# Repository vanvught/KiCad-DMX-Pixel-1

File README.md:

# KiCad DMX/RDM and Pixel 1-port 

Firmware 

- [https://github.com/vanvught/GD32F103RC-DMX512-RDM](https://github.com/vanvught/GD32F103RC-DMX512-RDM)
- [https://github.com/vanvught/GD32F107RC-DMX512-RDM](https://github.com/vanvught/GD32F107RC-DMX512-RDM)
- [https://github.com/vanvught/GD32F303RC-DMX512-RDM](https://github.com/vanvught/GD32F303RC-DMX512-RDM)

More information [https://www.gd32-dmx.org/pixel.html](https://www.gd32-dmx.org/pixel.html)

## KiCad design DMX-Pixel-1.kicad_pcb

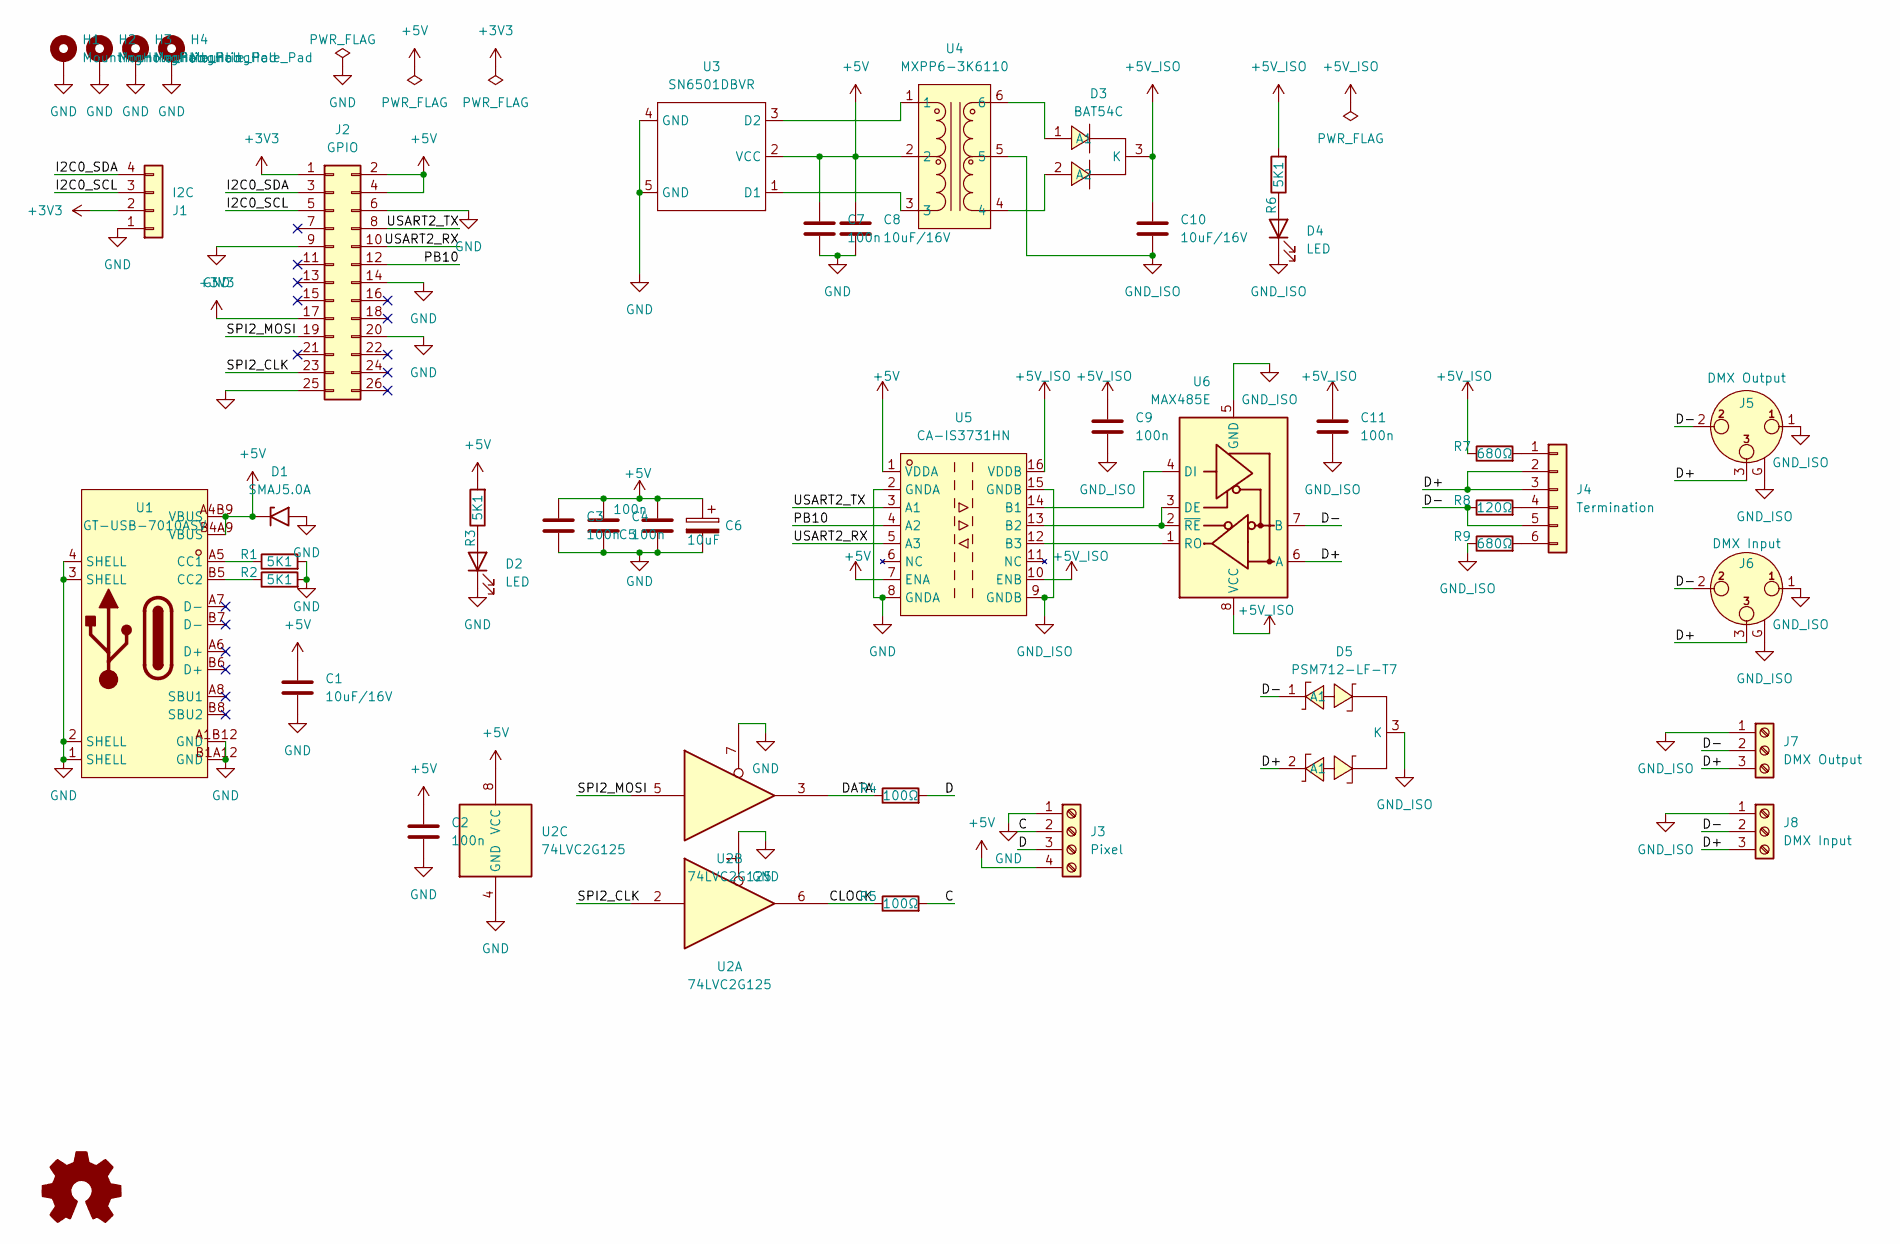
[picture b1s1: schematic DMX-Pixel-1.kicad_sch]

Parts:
C1, C8, C10: 10uF/16V; C_0603_1608Metric; LCSC Part C19702
C2, C3, C4, C5, C7, C9, C11: 100n; C_0603_1608Metric; LCSC Part C14663
C6: 10uF; CP_EIA-3216-18_Kemet-A; LCSC Part C7171
D1: SMAJ5.0A; D_SMA; LCSC Part C113952
D2, D4: LED; LED_0805_2012Metric; LCSC Part C2297
D3: BAT54C; SOT-23-3_L2.9-W1.6-P1.90-LS2.8-BR; MPN BAT54C; LCSC Part C2135
D5: PSM712-LF-T7; SOT-23-3_L3.0-W1.7-P0.95-LS2.9-BR; MPN PSM712-LF-T7; LCSC Part C32677
H1, H2, H3, H4: MountingHole_Pad; MountingHole_2.7mm_M2.5_Pad
J1: I2C; PinHeader_1x04_P2.54mm_Vertical
J2: GPIO; PinSocket_2x13_P2.54mm_Vertical
J3: Pixel; TerminalBlock_MetzConnect_Type094_RT03504HBLU_1x04_P5.00mm_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
J4: Termination; PinHeader_1x06_P2.54mm_Vertical
J5: DMX Output; Jack_XLR_Neutrik_NC3FAH2_Horizontal
J6: DMX Input; Jack_XLR_Neutrik_NC3MAH_Horizontal
J7: DMX Output; TerminalBlock_MetzConnect_Type094_RT03503HBLU_1x03_P5.00mm_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
J8: DMX Input; TerminalBlock_MetzConnect_Type094_RT03503HBLU_1x03_P5.00mm_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
R1, R2, R3, R6: 5K1; R_0603_1608Metric; LCSC Part C23186
R4, R5: 100Ω; R_0603_1608Metric; LCSC Part C22775
R7, R9: 680Ω; R_0603_1608Metric; LCSC Part C23228
R8: 120Ω; R_0603_1608Metric; LCSC Part C22787
SYM1: Logo_Open_Hardware_Small; OSHW-Logo_7.5x8mm_SilkScreen
U1: GT-USB-7010ASV; USB-C-SMD_G-SWITCH_GT-USB-7010ASV; MPN GT-USB-7010ASV; LCSC Part C2988369
U2: 74LVC2G125; SM8_L3.2-W2.9-P0.65-LS4.3-BR; LCSC Part C206035
U3: SN6501DBVR; SOT-23-5_L3.0-W1.7-P0.95-LS2.8-BR; MPN SN6501DBVR; LCSC Part C49451
U4: MXPP6-3K6110; XFMR-SMD_L7.1-W6.6-P2.54_LT31-120; MPN MXPP6-3K6110; LCSC Part C19943838
U5: CA-IS3731HN; SOIC-16_L9.9-W3.9-P1.27-LS6.0-BL; MPN CA-IS3731HN; LCSC Part C428880
U6: MAX485E; SOIC-8_3.9x4.9mm_P1.27mm; LCSC Part C23492

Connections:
+3V3: J1.2, J2.1, J2.17
+5V: C1.1, C2.1, C3.1, C4.1, C5.2, C6.1, C7.1, C8.1, D1.1 (A1), J2.2, J2.4, J3.4, R3.2, U1.A4B9 (VBUS), U1.B4A9 (VBUS), U2.8 (VCC), U3.2 (VCC), U4.2, U5.1 (VDDA), U5.7 (ENA)
+5V_ISO: C9.1, C10.1, C11.1, D3.3 (K), R6.2, R7.1, U5.10 (ENB), U5.16 (VDDB), U6.8 (VCC)
/C: J3.2, R5.2
/CLOCK: R5.1, U2.6
/D: J3.3, R4.2
/D+: D5.2 (A1), J4.2, J4.3, J5.3, J6.3, J7.3, J8.3, U6.6 (A)
/D-: D5.1 (A1), J4.5, J5.2, J6.2, J7.2, J8.2, R8.1, U6.7 (B)
/DATA: R4.1, U2.3
/I2C0_SCL: J1.3, J2.5
/I2C0_SDA: J1.4, J2.3
/PB10: J2.12, U5.4 (A2)
/SPI2_CLK: J2.23, U2.2
/SPI2_MOSI: J2.19, U2.5
/USART2_RX: J2.10, U5.5 (A3)
/USART2_TX: J2.8, U5.3 (A1)
GND: C1.2, C2.2, C3.2, C4.2, C5.1, C6.2, C7.2, C8.2, D1.2 (A2), D2.1 (K), H1.1 (1_1), H2.1 (1_1), H3.1 (1_1), H4.1 (1_1), J1.1, J2.6, J2.9, J2.14, J2.20, J2.25, J3.1, R1.2, R2.2, U1.1 (SHELL), U1.2 (SHELL), U1.3 (SHELL), U1.4 (SHELL), U1.A1B12 (GND), U1.B1A12 (GND), U2.1, U2.4 (GND), U2.7, U3.4 (GND), U3.5 (GND), U5.2 (GNDA), U5.8 (GNDA)
GND_ISO: C9.2, C10.2, C11.2, D4.1 (K), D5.3 (K), J5.1, J5.G, J6.1, J6.G, J7.1, J8.1, R9.1, U4.5, U5.9 (GNDB), U5.15 (GNDB), U6.5 (GND)
unnamed: D2.2 (A), R3.1
unnamed: D3.1 (A1), U4.6
unnamed: D3.2 (A2), U4.4
unnamed: D4.2 (A), R6.1
unnamed: J4.1, R7.2
unnamed: J4.4, R8.2
unnamed: J4.6, R9.2
unnamed: R1.1, U1.A5 (CC1)
unnamed: R2.1, U1.B5 (CC2)
unnamed: U3.1 (D1), U4.3
unnamed: U3.3 (D2), U4.1
unnamed: U5.14 (B1), U6.4 (DI)
unnamed: U5.13 (B2), U6.2 (~RE), U6.3 (DE)
unnamed: U5.12 (B3), U6.1 (RO)

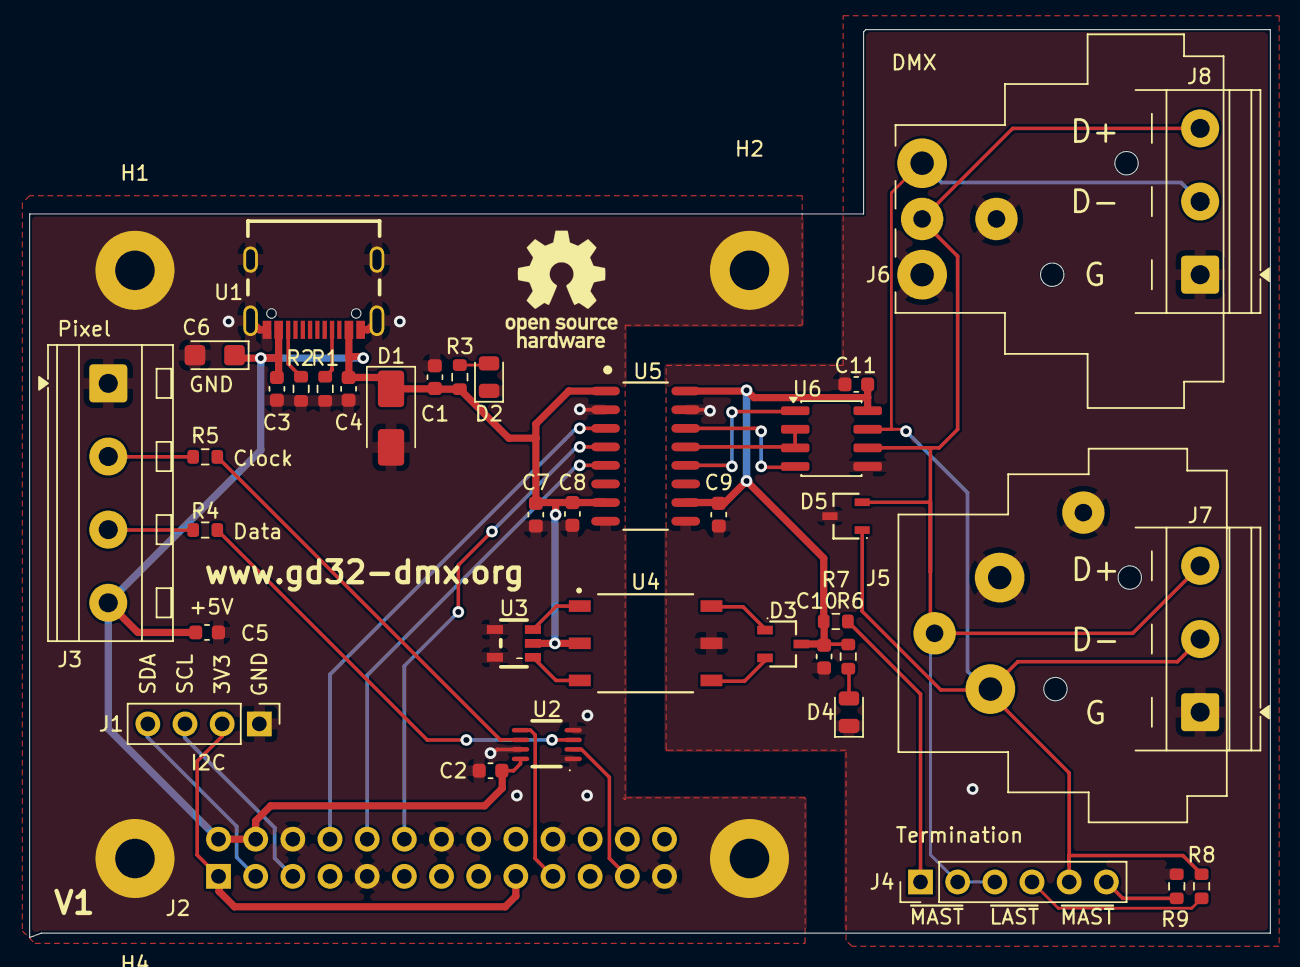
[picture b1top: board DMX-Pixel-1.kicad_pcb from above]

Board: 2 copper layers, 84.8 x 62.0 mm, 44 parts (1 on the bottom side), 32 nets.
